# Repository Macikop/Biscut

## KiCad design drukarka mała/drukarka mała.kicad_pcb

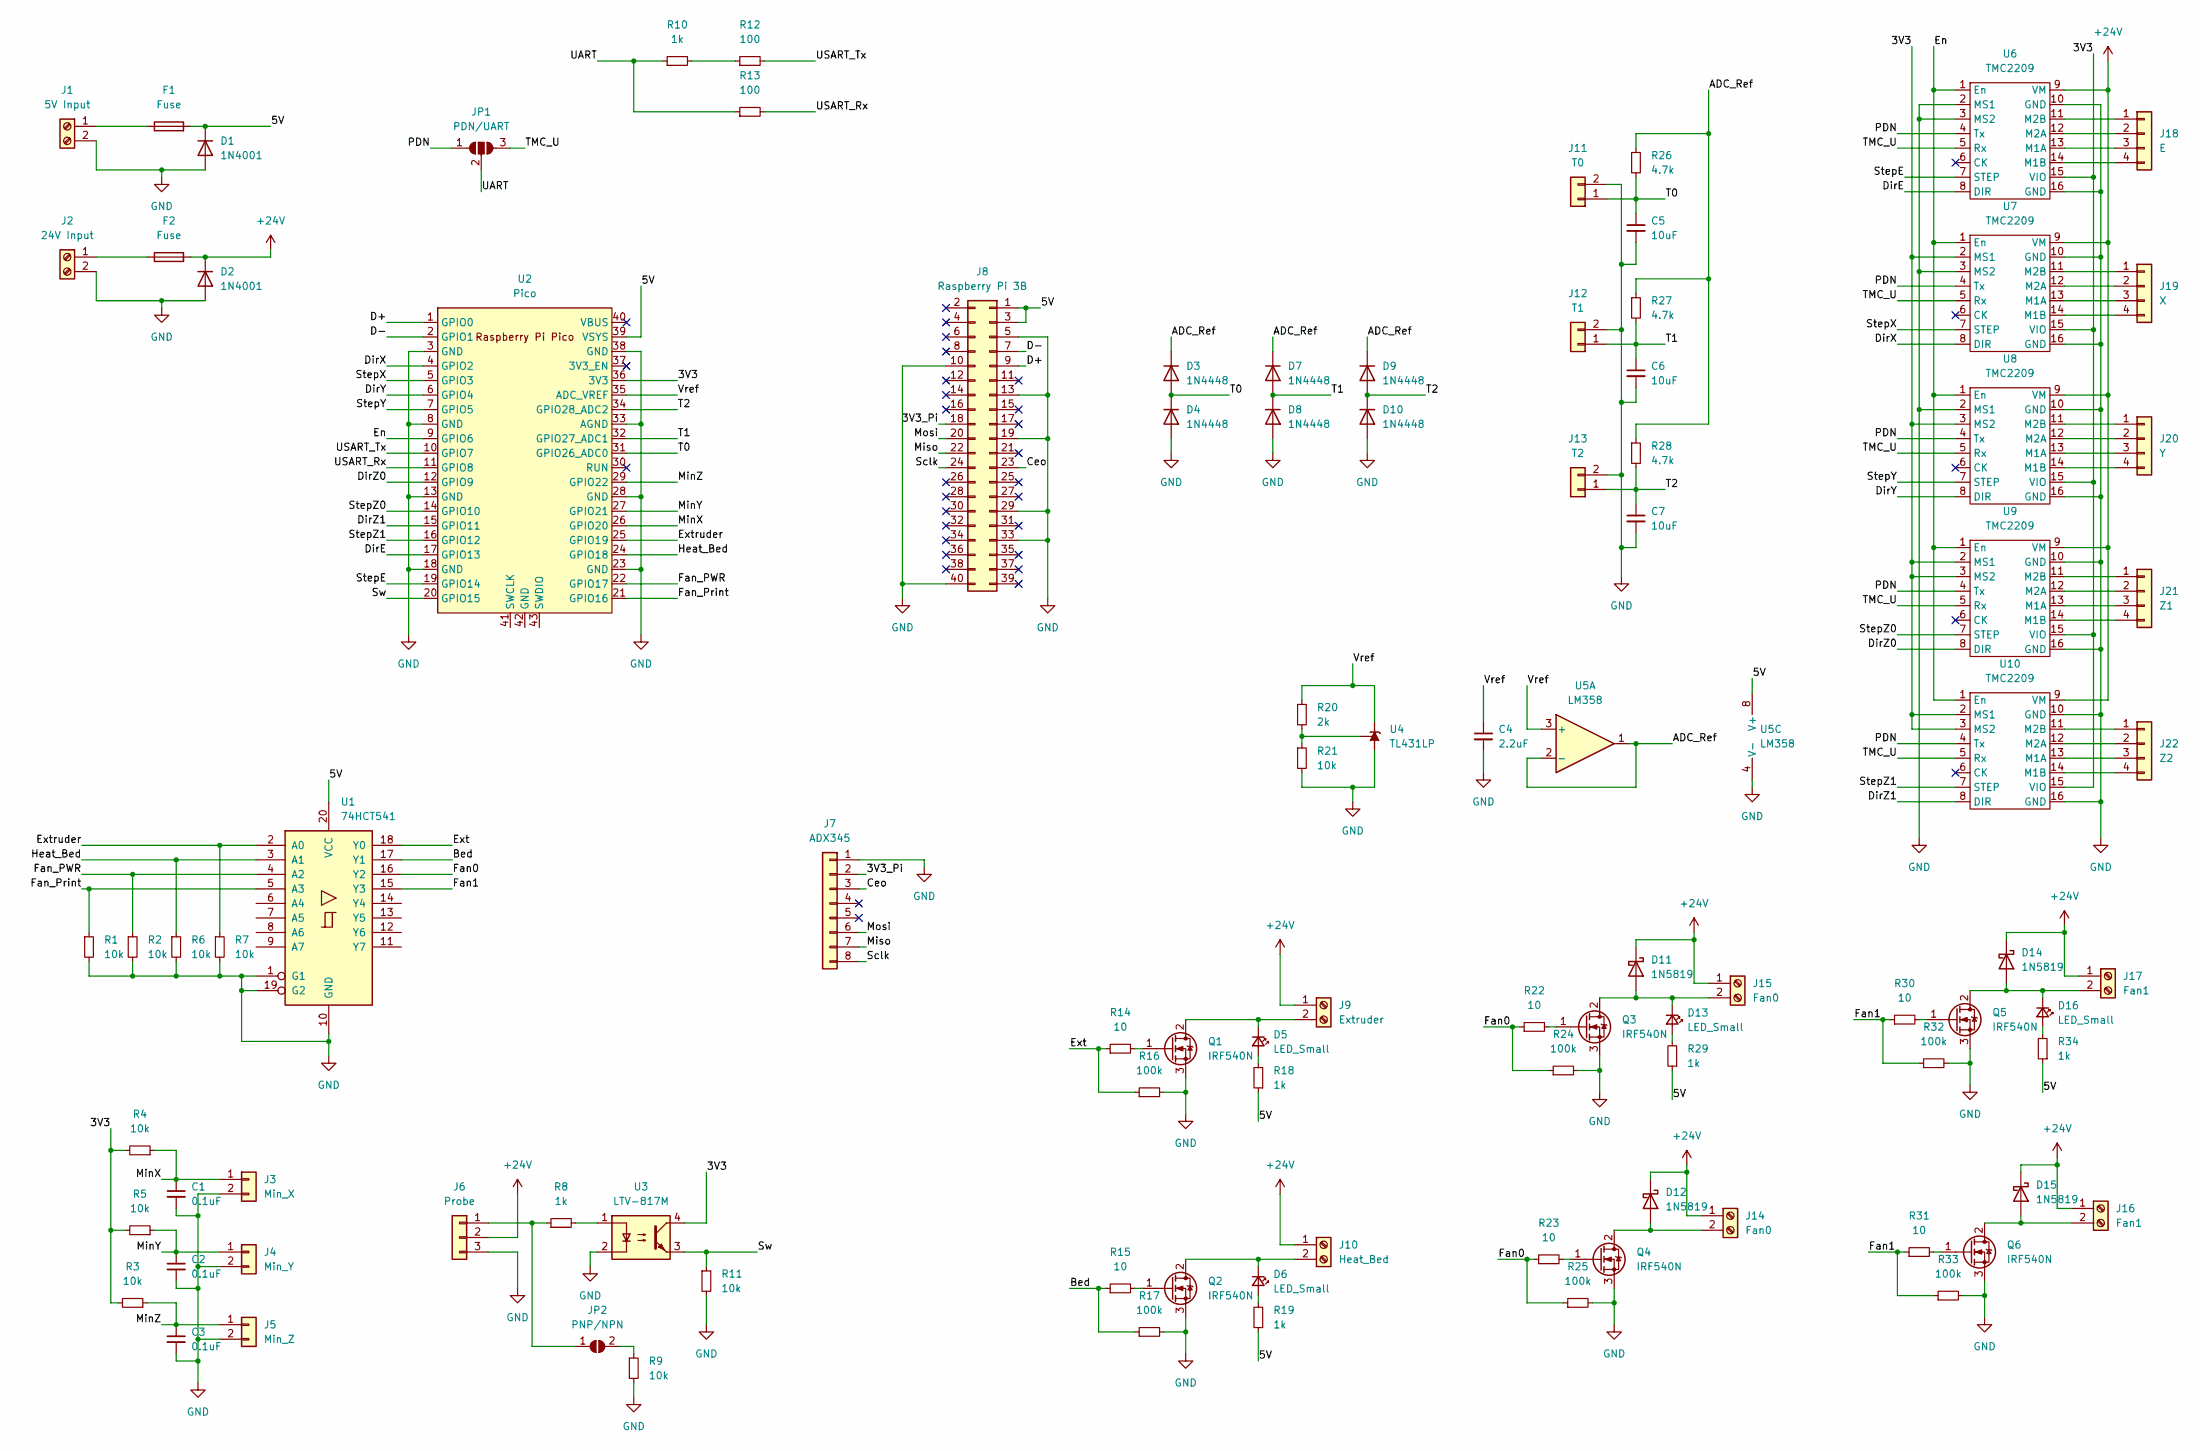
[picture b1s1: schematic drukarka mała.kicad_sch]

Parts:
C1, C2, C3: 0.1uF; C_Disc_D3.0mm_W1.6mm_P2.50mm
C4: 2.2uF; C_Radial_D5.0mm_H11.0mm_P2.00mm
C5, C6, C7: 10uF; C_Radial_D5.0mm_H11.0mm_P2.00mm
D1, D2: 1N4001; D_DO-41_SOD81_P10.16mm_Horizontal
D3, D4, D7, D8, D9, D10: 1N4448; D_DO-35_SOD27_P7.62mm_Horizontal
D5, D6, D13, D16: LED_Small; LED_D5.0mm
D11, D12, D14, D15: 1N5819; D_DO-41_SOD81_P10.16mm_Horizontal
F1, F2: Fuse; Fuseholder_Littelfuse_100_series_5x20mm
J1: 5V Input; TerminalBlock_Altech_AK300-2_P5.00mm
J2: 24V Input; TerminalBlock_Altech_AK300-2_P5.00mm
J3: Min_X; JST_EH_B2B-EH-A_1x02_P2.50mm_Vertical
J4: Min_Y; JST_EH_B2B-EH-A_1x02_P2.50mm_Vertical
J5: Min_Z; JST_EH_B2B-EH-A_1x02_P2.50mm_Vertical
J6: Probe; TerminalBlock_Altech_AK300-3_P5.00mm
J7: ADX345; PinHeader_1x08_P2.54mm_Vertical
J8: Raspberry Pi 3B; PinHeader_2x20_P2.54mm_Vertical
J9: Extruder; TerminalBlock_Altech_AK300-2_P5.00mm
J10: Heat_Bed; TerminalBlock_Altech_AK300-2_P5.00mm
J11: T0; JST_EH_B2B-EH-A_1x02_P2.50mm_Vertical
J12: T1; JST_EH_B2B-EH-A_1x02_P2.50mm_Vertical
J13: T2; JST_EH_B2B-EH-A_1x02_P2.50mm_Vertical
J14, J15: Fan0; JST_EH_B2B-EH-A_1x02_P2.50mm_Vertical
J16, J17: Fan1; JST_EH_B2B-EH-A_1x02_P2.50mm_Vertical
J18: E; JST_EH_B4B-EH-A_1x04_P2.50mm_Vertical
J19: X; JST_EH_B4B-EH-A_1x04_P2.50mm_Vertical
J20: Y; JST_EH_B4B-EH-A_1x04_P2.50mm_Vertical
J21: Z1; JST_EH_B4B-EH-A_1x04_P2.50mm_Vertical
J22: Z2; JST_EH_B4B-EH-A_1x04_P2.50mm_Vertical
JP1: PDN/UART; SolderJumper-3_P1.3mm_Open_RoundedPad1.0x1.5mm
JP2: PNP/NPN; SolderJumper-2_P1.3mm_Open_RoundedPad1.0x1.5mm
Q1, Q2, Q3, Q4, Q5, Q6: IRF540N; TO-220-3_Vertical
R1, R2, R3, R4, R5, R6, R7, R9, R11, R21: 10k; R_Axial_DIN0204_L3.6mm_D1.6mm_P7.62mm_Horizontal
R8, R10, R18, R19, R29, R34: 1k; R_Axial_DIN0204_L3.6mm_D1.6mm_P7.62mm_Horizontal
R12, R13: 100; R_Axial_DIN0204_L3.6mm_D1.6mm_P7.62mm_Horizontal
R14, R15, R22, R23, R30, R31: 10; R_Axial_DIN0204_L3.6mm_D1.6mm_P7.62mm_Horizontal
R16, R17, R24, R25, R32, R33: 100k; R_Axial_DIN0204_L3.6mm_D1.6mm_P7.62mm_Horizontal
R20: 2k; R_Axial_DIN0204_L3.6mm_D1.6mm_P7.62mm_Horizontal
R26, R27, R28: 4.7k; R_Axial_DIN0204_L3.6mm_D1.6mm_P7.62mm_Horizontal
U1: 74HCT541; DIP-20_W7.62mm_Socket_LongPads
U2: Pico; RPi_Pico_SMD_TH
U3: LTV-817M; DIP-4_W10.16mm
U4: TL431LP; TO-92_Inline
U5: LM358; DIP-8_W7.62mm_Socket_LongPads
U6, U7, U8, U9, U10: TMC2209

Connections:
+24V: D2.1 (K), D11.1 (K), D12.1 (K), D14.1 (K), D15.1 (K), F2.2, J6.2, J9.1, J10.1, J14.1, J15.1, J16.1, J17.1, U6.9 (VM), U7.9 (VM), U8.9 (VM), U9.9 (VM), U10.9 (VM)
/3V3: R3.2, R4.2, R5.2, U2.36 (3V3), U3.4, U6.15 (VIO), U7.2 (MS1), U7.15 (VIO), U8.3 (MS2), U8.15 (VIO), U9.2 (MS1), U9.3 (MS2), U9.15 (VIO), U10.2 (MS1), U10.3 (MS2), U10.15 (VIO)
/3V3_Pi: J7.2, J8.18
/5V: D1.1 (K), F1.2, J8.1, J8.3, R18.1, R19.1, R29.1, R34.1, U1.20 (VCC), U2.39 (VSYS), U5.8 (V+)
/ADC_Ref: D3.1 (K), D7.1 (K), D9.1 (K), R26.1, R27.1, R28.1, U5.1, U5.2 (-)
/Bed: R15.1, R17.1, U1.17 (Y1)
/Ceo: J7.3, J8.23
/D+: J8.9, U2.1 (GPIO0)
/D-: J8.7, U2.2 (GPIO1)
/DirE: U2.17 (GPIO13), U6.8 (DIR)
/DirX: U2.4 (GPIO2), U7.8 (DIR)
/DirY: U2.6 (GPIO4), U8.8 (DIR)
/DirZ0: U2.12 (GPIO9), U9.8 (DIR)
/DirZ1: U2.15 (GPIO11), U10.8 (DIR)
/En: U2.9 (GPIO6), U6.1 (En), U7.1 (En), U8.1 (En), U9.1 (En), U10.1 (En)
/Ext: R14.1, R16.1, U1.18 (Y0)
/Extruder: R7.1, U1.2 (A0), U2.25 (GPIO19)
/Fan0: R22.1, R23.1, R24.1, R25.1, U1.16 (Y2)
/Fan1: R30.1, R31.1, R32.1, R33.1, U1.15 (Y3)
/Fan_PWR: R2.1, U1.4 (A2), U2.22 (GPIO17)
/Fan_Print: R1.1, U1.5 (A3), U2.21 (GPIO16)
/Heat_Bed: R6.1, U1.3 (A1), U2.24 (GPIO18)
/MinX: C1.1, J3.1, R4.1, U2.26 (GPIO20)
/MinY: C2.1, J4.1, R5.1, U2.27 (GPIO21)
/MinZ: C3.1, J5.1, R3.1, U2.29 (GPIO22)
/Miso: J7.7, J8.22
/Mosi: J7.6, J8.20
/PDN: JP1.1 (A), U6.4 (Tx), U7.4 (Tx), U8.4 (Tx), U9.4 (Tx), U10.4 (Tx)
/Sclk: J7.8, J8.24
/StepE: U2.19 (GPIO14), U6.7 (STEP)
/StepX: U2.5 (GPIO3), U7.7 (STEP)
/StepY: U2.7 (GPIO5), U8.7 (STEP)
/StepZ0: U2.14 (GPIO10), U9.7 (STEP)
/StepZ1: U2.16 (GPIO12), U10.7 (STEP)
/Sw: R11.1, U2.20 (GPIO15), U3.3
/T0: C5.1, D3.2 (A), D4.1 (K), J11.1, R26.2, U2.31 (GPIO26_ADC0)
/T1: C6.1, D7.2 (A), D8.1 (K), J12.1, R27.2, U2.32 (GPIO27_ADC1)
/T2: C7.1, D9.2 (A), D10.1 (K), J13.1, R28.2, U2.34 (GPIO28_ADC2)
/TMC_U: JP1.3 (B), U6.5 (Rx), U7.5 (Rx), U8.5 (Rx), U9.5 (Rx), U10.5 (Rx)
/UART: JP1.2 (C), R10.1, R13.1
/USART_Rx: R13.2, U2.11 (GPIO8)
/USART_Tx: R12.2, U2.10 (GPIO7)
/Vref: C4.1, R20.1, U2.35 (ADC_VREF), U4.3 (K), U5.3 (+)
GND: C1.2, C2.2, C3.2, C4.2, C5.2, C6.2, C7.2, D1.2 (A), D2.2 (A), D4.2 (A), D8.2 (A), D10.2 (A), J1.2, J2.2, J3.2, J4.2, J5.2, J6.3, J7.1, J8.5, J8.10, J8.13, J8.19, J8.29, J8.33, J8.40, J11.2, J12.2, J13.2, Q1.3 (S), Q2.3 (S), Q3.3 (S), Q4.3 (S), Q5.3 (S), Q6.3 (S), R1.2, R2.2, R6.2, R7.2, R9.2, R11.2, R16.2, R17.2, R21.2, R24.2, R25.2, R32.2, R33.2, U1.1 (G1), U1.10 (GND), U1.19 (G2), U2.3 (GND), U2.8 (GND), U2.13 (GND), U2.18 (GND), U2.23 (GND), U2.28 (GND), U2.33 (AGND), U2.38 (GND), U3.2, U4.2 (A), U5.4 (V-), U6.2 (MS1), U6.3 (MS2), U6.10 (GND), U6.16 (GND), U7.3 (MS2), U7.10 (GND), U7.16 (GND), U8.2 (MS1), U8.10 (GND), U8.16 (GND), U9.10 (GND), U9.16 (GND), U10.10 (GND), U10.16 (GND)
unnamed: D5.1 (K), J9.2, Q1.2 (D)
unnamed: D5.2 (A), R18.2
unnamed: D6.1 (K), J10.2, Q2.2 (D)
unnamed: D6.2 (A), R19.2
unnamed: D11.2 (A), D13.1 (K), J15.2, Q3.2 (D)
unnamed: D12.2 (A), J14.2, Q4.2 (D)
unnamed: D13.2 (A), R29.2
unnamed: D14.2 (A), D16.1 (K), J17.2, Q5.2 (D)
unnamed: D15.2 (A), J16.2, Q6.2 (D)
unnamed: D16.2 (A), R34.2
unnamed: F1.1, J1.1
unnamed: F2.1, J2.1
unnamed: J6.1, JP2.1 (A), R8.1
unnamed: J18.1, U6.11 (M2B)
unnamed: J18.2, U6.12 (M2A)
unnamed: J18.3, U6.13 (M1A)
unnamed: J18.4, U6.14 (M1B)
unnamed: J19.1, U7.11 (M2B)
unnamed: J19.2, U7.12 (M2A)
unnamed: J19.3, U7.13 (M1A)
unnamed: J19.4, U7.14 (M1B)
unnamed: J20.1, U8.11 (M2B)
unnamed: J20.2, U8.12 (M2A)
unnamed: J20.3, U8.13 (M1A)
unnamed: J20.4, U8.14 (M1B)
unnamed: J21.1, U9.11 (M2B)
unnamed: J21.2, U9.12 (M2A)
unnamed: J21.3, U9.13 (M1A)
unnamed: J21.4, U9.14 (M1B)
unnamed: J22.1, U10.11 (M2B)
unnamed: J22.2, U10.12 (M2A)
unnamed: J22.3, U10.13 (M1A)
unnamed: J22.4, U10.14 (M1B)
unnamed: JP2.2 (B), R9.1
unnamed: Q1.1 (G), R14.2
unnamed: Q2.1 (G), R15.2
unnamed: Q3.1 (G), R22.2
unnamed: Q4.1 (G), R23.2
unnamed: Q5.1 (G), R30.2
unnamed: Q6.1 (G), R31.2
unnamed: R8.2, U3.1
unnamed: R10.2, R12.1
unnamed: R20.2, R21.1, U4.1 (REF)

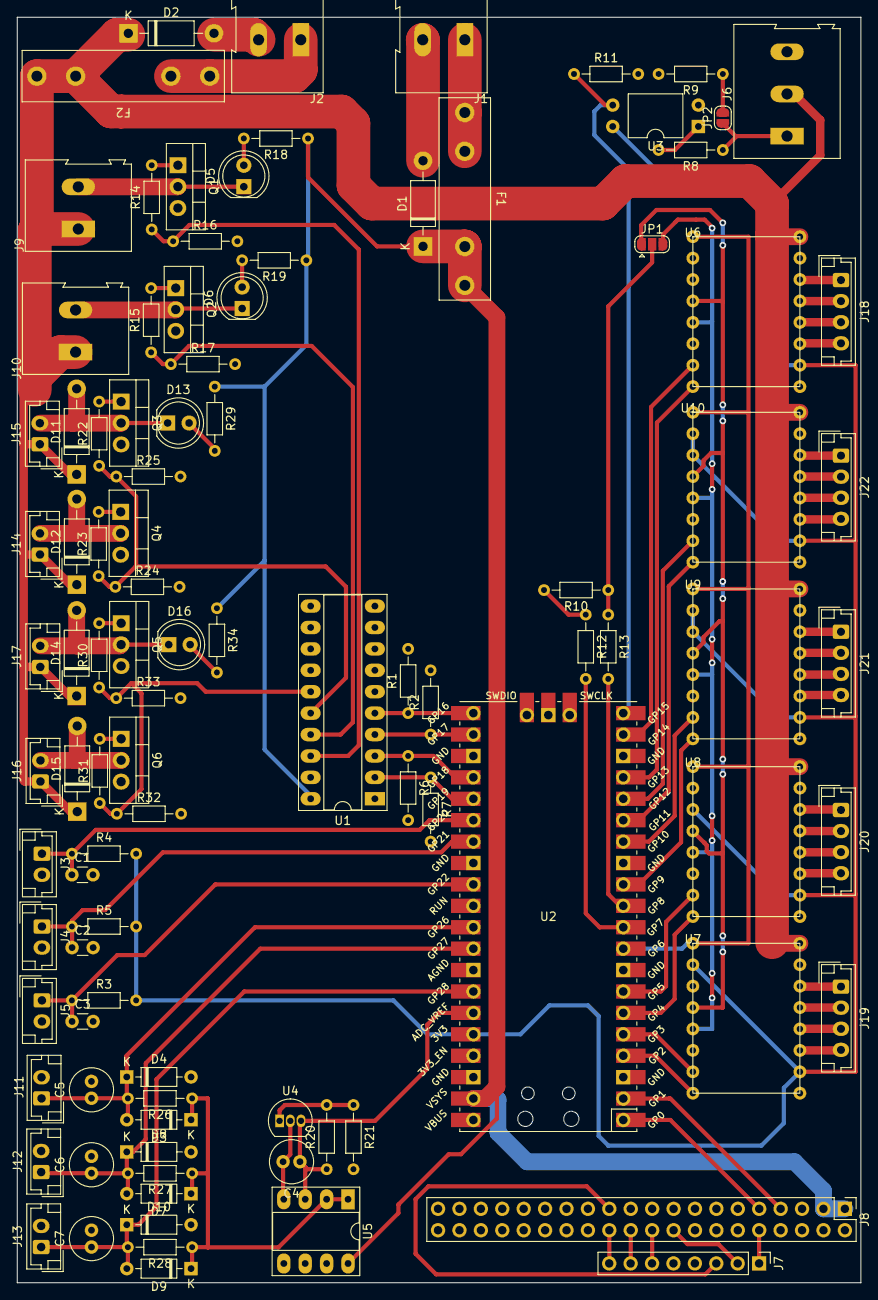
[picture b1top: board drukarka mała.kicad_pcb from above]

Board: 2 copper layers, 100.1 x 150.1 mm, 99 parts (0 on the bottom side), 87 nets.

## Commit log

2023-02-23 Add files via upload
    Initial commit
